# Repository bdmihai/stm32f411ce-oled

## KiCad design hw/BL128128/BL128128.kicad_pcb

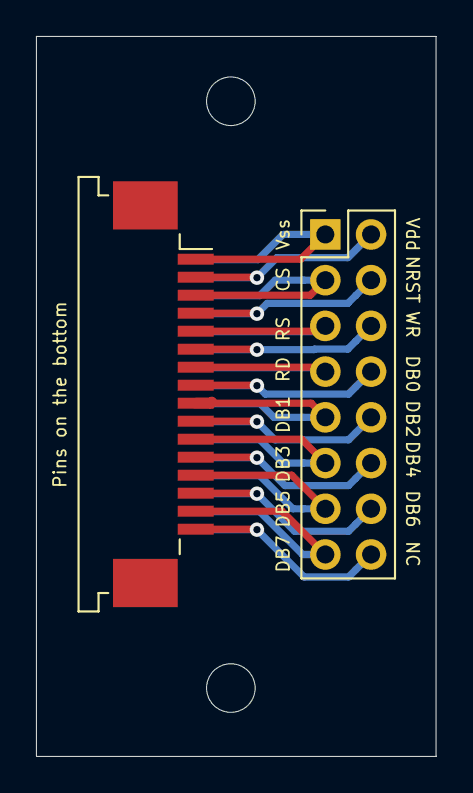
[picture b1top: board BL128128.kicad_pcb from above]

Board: 2 copper layers, 22.2 x 40.0 mm, 5 parts (1 on the bottom side), 16 nets.

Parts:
H1, H2: MountingHole; MountingHole_2.7mm_M2.5
J1: Conn_02x08_Odd_Even; PinHeader_2x08_P2.54mm_Vertical
J2, J3: Conn_01x16; TE_1-84952-6_1x16-1MP_P1.0mm_Horizontal

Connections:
CS: J1.3, J2.3, J3.14
DB0: J1.8, J2.8, J3.9
DB1: J1.9, J2.9, J3.8
DB2: J1.10, J2.10, J3.7
DB3: J1.11, J2.11, J3.6
DB4: J1.12, J2.12, J3.5
DB5: J1.13, J2.13, J3.4
DB6: J1.14, J2.14, J3.3
DB7: J1.15, J2.15, J3.2
NC: J1.16, J2.16, J3.1
NRST: J1.4, J2.4, J3.13
RD: J1.7, J2.7, J3.10
RS: J1.5, J2.5, J3.12
Vdd: J1.2, J2.2, J3.15
Vss: J1.1, J2.1, J3.16
WR: J1.6, J2.6, J3.11

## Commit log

2021-01-08 Initial revision
2021-01-09 Small refactoring
2021-01-13 updated astyle
2022-05-14 compile with qbs 1.22
